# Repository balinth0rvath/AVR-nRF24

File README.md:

# RF Communication Mesh
### What is This?
A sensor network consisting a server running on a Pi and several environmental sensors based on AVR MCU's. These things are communicating each other via RF and the sensors are planned to work through a season with one charge of a 3.6V battery.  

---

### Code Structure
|Description|Module|
|------|-----------|
|Custom nRF24L01 driver in my forked Linux repo located in nRF24L01driver branch|https://github.com/balinth0rvath/linux/tree/nRF24L01driver|
|Server app and unit tests|https://github.com/balinth0rvath/AVR-nRF24/tree/master/server|
|HW related stuff (Schematics, gerber files etc...)|https://github.com/balinth0rvath/AVR-nRF24/tree/master/nRF24-design|
|Firmware of a sensor module|https://github.com/balinth0rvath/AVR-nRF24/tree/master/AVR-nRF24|

---

### Server UML

---

### Schematics

---

### Current Dev Setup (Mid of September 2021)

---

### Breadboard in Early Stage

---

### First Prototypes without Sensors

---

### Debug Screenshot, DS18B20 Sequence of Determining External Power Supply Mode

---
## Setup
### Init Yocto Build
```
$ mkdir rpi
$ cd rpi
$ git clone -b gatesgarth git://git.yoctoproject.org/poky.git
$ git clone -b gatesgarth git://git.openembedded.org/meta-openembedded
$ git clone -b gatesgarth git://git.openembedded.org/meta-raspberrypi
$ source poky/oe-init-build-env ./build
```
./build/conf/bblayers.conf
```
# POKY_BBLAYERS_CONF_VERSION is increased each time build/conf/bblayers.conf
# changes incompatibly
POKY_BBLAYERS_CONF_VERSION = "2" 

BBPATH = "${TOPDIR}"
BBFILES ?= ""

BBLAYERS ?= " \ 
  ~/yocto-builds/rpi/poky/meta \
  ~/yocto-builds/rpi/poky/meta-poky \
  ~/yocto-builds/rpi/poky/meta-yocto-bsp \
  ~/yocto-builds/rpi/meta-raspberrypi \
  ~/yocto-builds/rpi/meta-openembedded/meta-oe \
  ~/yocto-builds/rpi/meta-openembedded/meta-python \
  ~/yocto-builds/rpi/meta-openembedded/meta-networking \
  ~/yocto-builds/rpi/meta-openembedded/meta-multimedia \
  ~/yocto-builds/rpi/meta-openembedded/meta-filesystems \
  "
```

./build/conf/local.conf
```
...
MACHINE ??= "raspberrypi3"
...
DISTRO_FEATURES_append = "bluez5 bluetooth wifi systemd"
VIRTUAL-RUNTIME_init_manager = "systemd"
IMAGE_INSTALL_append = "crda iw bluez5 wpa-supplicant openssh"
```

### Create SD Card Image and SDK
```
$ cd rpi
$ . poky/oe-init-build-env
$ bitbake core-image-minimal
$ bitbake core-image-minimal -c populate_sdk
$ tmp/deploy/sdk/poky-glibc-x86_64-core-image-minimal-cortexa7t2hf-neon-vfpv4-raspberrypi3-toolchain-3.2.2.sh
```

### Install Packages
```
$ sudo apt-get install libssl-dev
```

### Build Kernel
```
$ cd <linux source root>
$ . /opt/poky/3.2.2/environment-setup-cortexa7t2hf-neon-vfpv4-poky-linux-gnueabi 
$ KERNEL=kernel7
$ make ARCH=arm CROSS_COMPILE=arm-poky-linux-gnueabi- bcm2709_defconfig
$ make ARCH=arm CROSS_COMPILE=arm-poky-linux-gnueabi- zImage modules dtbs
```

### Build Driver
```
$ cd <linux source root>
$ . /opt/poky/3.2.2/environment-setup-cortexa7t2hf-neon-vfpv4-poky-linux-gnueabi 
$ make ARCH=arm CROSS_COMPILE=arm-poky-linux-gnueabi- -C . M=drivers/char/nrf24/
$ scp nrf24.ko root@<IP of PI>:/home/root/.
```

### Server Setup
```
$ cd server
$ . /opt/poky/3.2.2/environment-setup-cortexa7t2hf-neon-vfpv4-poky-linux-gnueabi
$ make lib/libwireless.a
$ make
$ make test
$ scp server root@<IP of PI>:/home/root/.
$ scp test root@<IP of PI>:/home/root/.
```

### Server Init
```
$ insmod nrf24.ko
$ ./test
$ ./server
```

---

## Remote Debug Server
Target
```
$ gdbserver :1234 server
```
Host
```
$ arm-poky-linux-gnueabi-gdb server
(gdb) target remote <IP of PI>:1234
```
---

## Release Commits (Test Longloop)
A test named Test Longloop must pass in all release commits.
|Releas Date|Driver Branch and Commit Hash<br>Firmware and Design Branch and Commit Hash|
|----|---|
|20210517|linux@nRF24L01driver:8a4c0cdf7803df328cc4730b5077f52fee5dc932<br>AVR-nRF24@master:3eb939d17d8ff22d65403e109d810f7f85f86c85|
|20210523|linux@nRF24L01driver:8a4c0cdf7803df328cc4730b5077f52fee5dc932<br>AVR-nRF24@master:7b25dc61fc849677e8bb6358456cee5dc74c7301|
|20210531|linux@nRF24L01driver:7c86b9ca6b2d7ad1549c76c9caeeb97bab567bfb<br>AVR-nRF24@master:dd0c3b836620fbdc131a8c8d285148fa6ca5f2e6|
|20210820|inux@nRF24L01driver:7c86b9ca6b2d7ad1549c76c9caeeb97bab567bfb<br>AVR-nRF24@master:85c61a1c3e08124cf29ecca4751b73a7c155e9e8|
|20210909|linux@nRF24L01driver:f5a8eb844164f856415a3b459346a1253c0f87ff<br>AVR-nRF24@master:ca4479ed1e2c967fedf4eaf3a40d907f1cda15d0|
|20210919|linux@nRF24L01driver:f5a8eb844164f856415a3b459346a1253c0f87ff<br>AVR-nRF24@master:d2804b9a1e1fc83868c6ceb204d5eec31b9cb42f|

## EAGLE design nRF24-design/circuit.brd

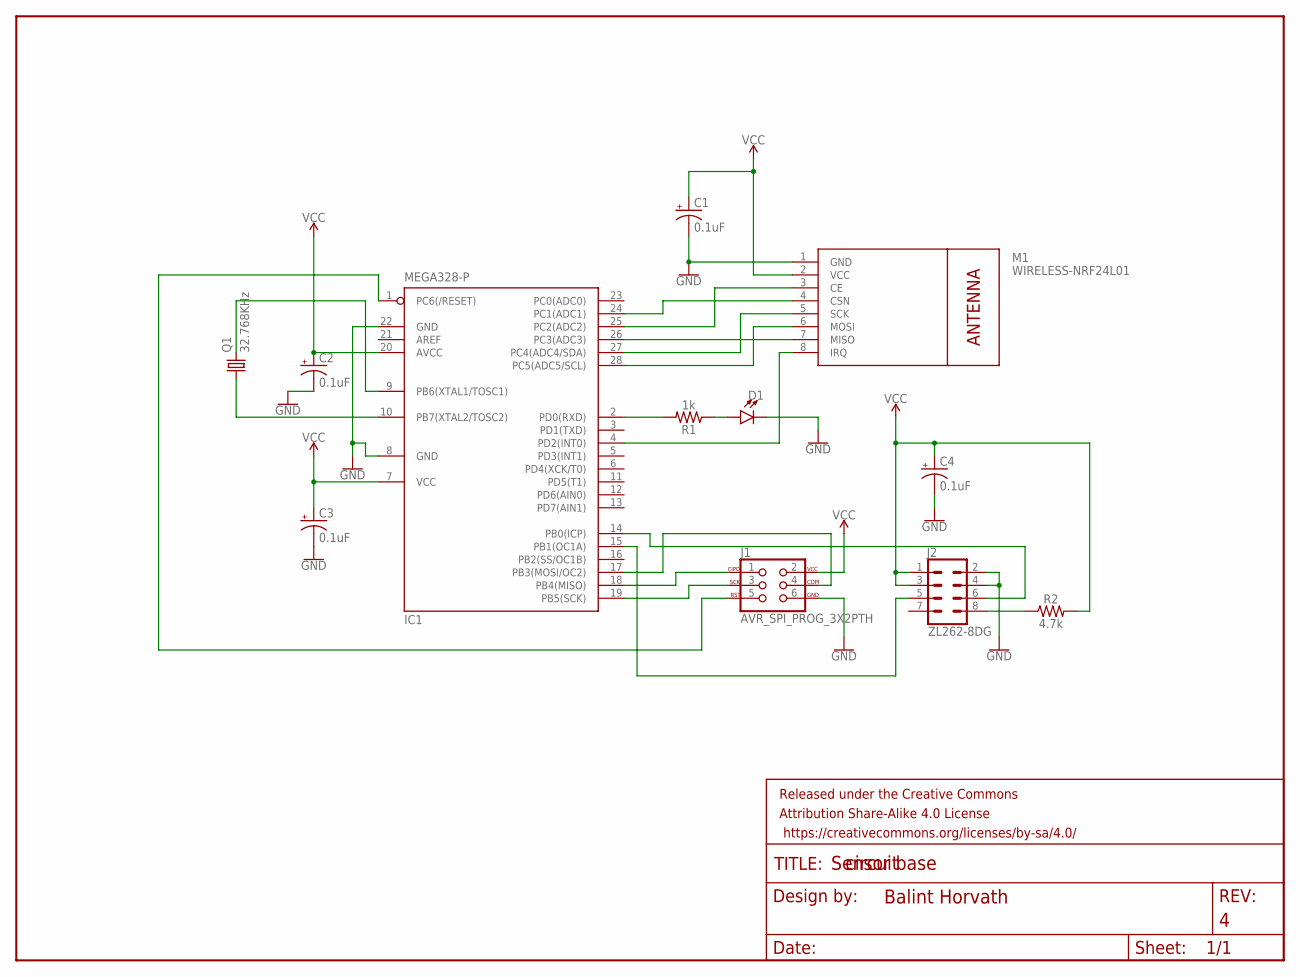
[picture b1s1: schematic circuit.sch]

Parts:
C1, C2, C3, C4: 0.1uF; CPOL-RADIAL-2.5MM-5MM
D1: LED5MM; LED_5MM
FRAME1: FRAME-LETTER; CREATIVE_COMMONS
IC1: MEGA328-P; DIL28-3
J1: AVR_SPI_PROG_3X2PTH; 2X3
J2: ZL262-8DG; 2X4
M1: WIRELESS-NRF24L01
Q1: 32.768KHz; TC26V
R1: 1k; AXIAL-0.3
R2: 4.7k; AXIAL-0.3

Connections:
GND: C1.2 (-), C2.2 (-), C3.2 (-), C4.2 (-), D1.K (C), IC1.8 (GND), IC1.22 (GND), J1.6, J2.2, J2.4, M1.1 (GND)
unnamed: IC1.9 (PB6(XTAL1/TOSC1)), Q1.2
unnamed: IC1.10 (PB7(XTAL2/TOSC2)), Q1.1
unnamed: IC1.2 (PD0(RXD)), R1.P$2 (2)
unnamed: D1.A, R1.P$1 (1)
unnamed: IC1.27 (PC4(ADC4/SDA)), M1.5 (SCK)
unnamed: IC1.4 (PD2(INT0)), M1.8 (IRQ)
unnamed: IC1.24 (PC1(ADC1)), M1.4 (CSN)
unnamed: IC1.26 (PC3(ADC3)), M1.7 (MISO)
unnamed: IC1.25 (PC2(ADC2)), M1.3 (CE)
unnamed: IC1.28 (PC5(ADC5/SCL)), M1.6 (MOSI)
unnamed: IC1.19 (PB5(SCK)), J1.3
unnamed: IC1.18 (PB4(MISO)), J1.1
unnamed: IC1.1 (PC6(/RESET)), J1.5
unnamed: IC1.17 (PB3(MOSI/OC2)), J1.4
unnamed: IC1.15 (PB1(OC1A)), J2.5
unnamed: J2.8, R2.P$1 (1)
unnamed: IC1.14 (PB0(ICP)), J2.6
VCC: C1.1 (+), C2.1 (+), C3.1 (+), C4.1 (+), IC1.7 (VCC), IC1.20 (AVCC), J1.2, J2.1, J2.3, M1.2 (VCC), R2.P$2 (2)

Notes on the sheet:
Sensor base

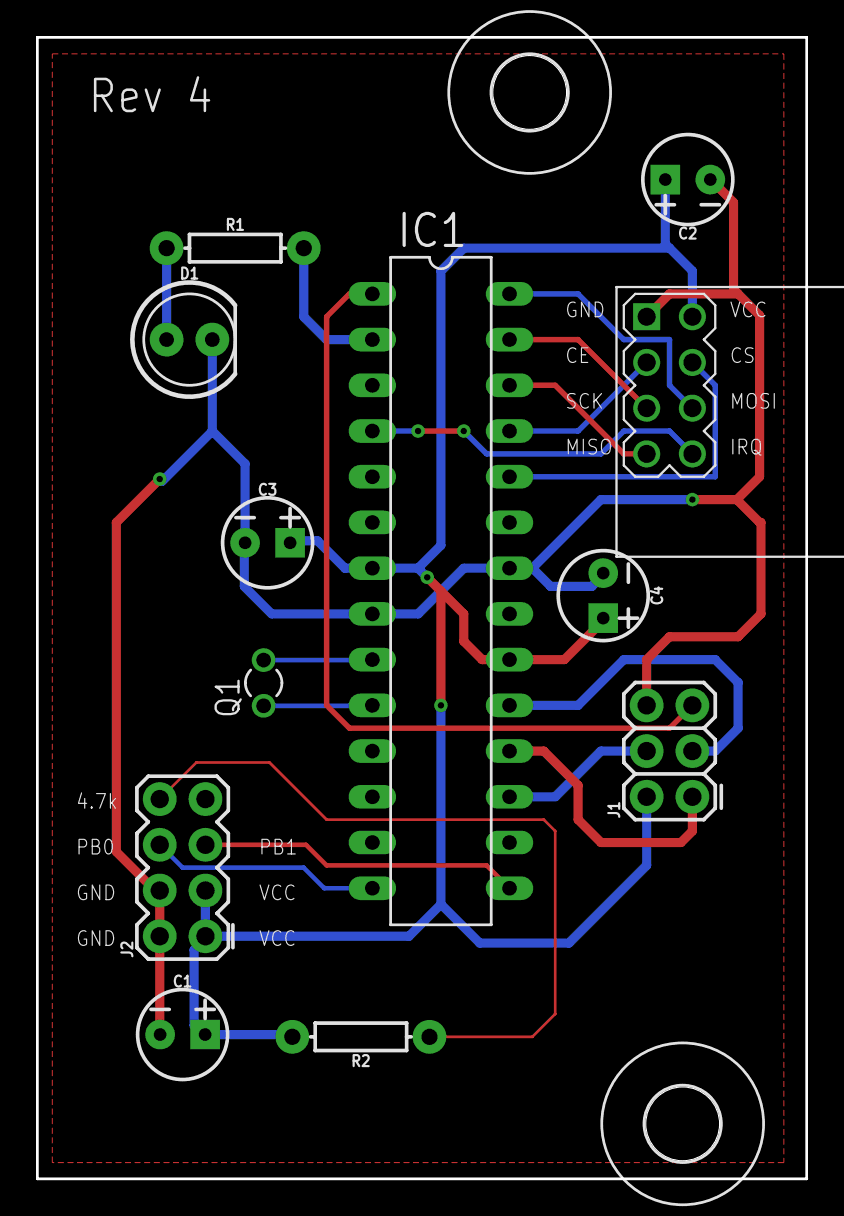
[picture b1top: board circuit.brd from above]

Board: 2 copper layers, 42.7 x 63.4 mm, 15 parts (0 on the bottom side), 19 nets.

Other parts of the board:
U$1, U$2: 4,1

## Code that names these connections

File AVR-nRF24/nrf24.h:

/*
 * nrf24.h
 *
 * Created: 4/30/2021 4:40:18 PM
 */ 


#ifndef NRF24_H_
#define NRF24_H_

#include <avr/io.h>

// Settings
#define NRF24_SET_RECEIVER                0x1
#define NRF24_PAYLOAD_LENGTH              0x4
#define NRF24_PAYLOAD_BUFFER_SIZE         0x50  

// SPI Port
#define NRF24_DDR                         DDRC
#define NRF24_PORT                        PORTC
#define NRF24_PIN                         PINC

// IRQ Port
#define NRF24_DDR_IRQ                     DDRD
#define NRF24_PORT_IRQ                    PORTD

// SPI&CE pin settings
#define NRF24_GPIO_CE                     PC2							
#define NRF24_GPIO_SCLK                   PC4								
#define NRF24_GPIO_MOSI                   PC5								
#define NRF24_GPIO_CSN                    PC1								
#define NRF24_GPIO_MISO                   PC3							
#define NRF24_SPI_HALF_CLK                1							

// IRQ pin settings
#define NRF24_GPIO_IRQ                    PD2								

// nRF24 commands
#define NRF24_CMD_R_REGISTER              0x00
#define NRF24_CMD_W_REGISTER              0x20
#define NRF24_CMD_R_RX_PAYLOAD            0x61
#define NRF24_CMD_W_TX_PAYLOAD            0xa0
#define NRF24_CMD_FLUSH_TX                0xe1
#define NRF24_CMD_FLUSH_RX                0xe2
#define NRF24_CMD_REUSE_TX_PL             0xe3
#define NRF24_CMD_ACTIVATE                0x50
#define NRF24_CMD_R_RX_PL_WID             0x60
#define NRF24_CMD_W_ACK_PAYLOAD           0xa8
#define NRF24_CMD_W_TX_PAYLOAD_NO_ACK			0xb0
#define NRF24_CMD_NOP                     0xff

// nRF24 registers
#define NRF24_REG_CONFIG                  0x00
#define NRF24_REG_EN_AA                   0x01
#define NRF24_REG_EN_RXADDR               0x02
#define NRF24_REG_SETUP_AW                0x03
#define NRF24_REG_SETUP_RETR              0x04
#define NRF24_REG_RF_CH                   0x05
#define NRF24_REG_RF_SETUP                0x06
#define NRF24_REG_STATUS                  0x07
#define NRF24_REG_OBSERVE_TX              0x08
#define NRF24_REG_CD                      0x09
#define NRF24_REG_RX_ADDR_P0              0x0a
#define NRF24_REG_RX_ADDR_P1              0x0b
#define NRF24_REG_RX_ADDR_P2              0x0c
#define NRF24_REG_RX_ADDR_P3              0x0d
#define NRF24_REG_RX_ADDR_P4              0x0e
#define NRF24_REG_RX_ADDR_P5              0x0f
#define NRF24_REG_TX_ADDR                 0x10
#define NRF24_REG_RX_PW_P0                0x11
#define NRF24_REG_RX_PW_P1                0x12
#define NRF24_REG_RX_PW_P2                0x13
#define NRF24_REG_RX_PW_P3                0x14
#define NRF24_REG_RX_PW_P4                0x15
#define NRF24_REG_RX_PW_P5                0x16
#define NRF24_REG_FIFO_STATUS             0x17
#define NRF24_REG_DYNPD                   0x1c
#define NRF24_REG_FEATURE                 0x1d

#define NRF24_REG_STATUS_DEFAULT          0x0e

typedef struct  {
	uint8_t id;
	uint8_t source_address;
	uint8_t value;
	uint8_t aux;
} nrf24_payload_buffer_item_t;

void nrf24_init(uint8_t use_spi);
int nrf24_check_device();
void nrf24_set_receiver();
void nrf24_set_transmitter();
void nrf24_set_rx_address_p0(uint8_t* address);
void nrf24_set_tx_address(uint8_t* address);
void nrf24_get_rx_address_p0(uint8_t* address);
void nrf24_get_tx_address(uint8_t* address);
void nrf24_receive_irq(void);
void nrf24_transmit_irq(void);
void nrf24_receive_poll(void);
void nrf24_transmit_packet(char* payload, uint8_t* status);
void nrf24_flush_tx(void);
void nrf24_flush_rx(void);
void nrf24_get_buffer_head(nrf24_payload_buffer_item_t* item);
uint8_t nrf24_get_status(void);
uint8_t nrf4_message_received(void);

#endif /* NRF24_H_ */

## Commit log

2021-04-30 Setup Atmel Studio
2021-04-30 nrf24: Implement basic bitbang driver functions
2021-04-30 Create LICENSE
2021-05-01 Fix bugs in nrf24 init
2021-05-01 Fix bug with MISO pin
2021-05-02 Create basic receiver. Refactor code
2021-05-03 Refactor code. Replace 16bit variables with 8bit, if possibble
2021-05-03 Implement transmitter
2021-05-04 Transmitter MVP
2021-05-05 Implement indicators
2021-05-07 Implement interrupt handling
2021-05-07 Implement interrupt handling in tx mode too
2021-05-07 Prepare switching between built in SPI and bitbang SPI
2021-05-08 Use HW SPI
2021-05-08 Check HW SPI receiver. Put half cycle wait into bb
2021-05-10 Implement ring buffer
2021-05-14 Separate receiver and transmitter
2021-05-16 Implement handshaking
2021-05-17 Prepare test
2021-05-17 Add unit test
2021-05-19 Prepare test framework
2021-05-22 Implement structure of test cases. Implement open driver test case
2021-05-23 Implement test cases
2021-05-23 Upload schematics
2021-05-23 Setup indicator led. Set, get RXP0, TX addresses
2021-05-23 Fix test lib link
2021-05-23 Add binaries to gitignore
2021-05-30 Add setup hint for MCU
2021-05-30 Use LED blinking for feedback
2021-05-30 New tests with different addresses
2021-05-30 Match address with tests
2021-05-30 Investigate address problem
2021-05-30 Investigate address problem - tests
2021-05-30 Create repeated test
2021-05-30 Tune timing
2021-05-30 Tune test parameters
2021-05-31 Refactor code
2021-05-31 Setup test cases with new address
2021-05-31 Setup MCU with matching address
2021-05-31 Update release list
2021-08-15 Add eagle files
2021-08-17 Finish schematics. Create board files. Create Gerber files
2021-08-17 Fix design. Add image of schematics
2021-08-17 Create Gerber files
2021-08-17 Create Gerber files for jlcpcb
2021-08-19 Create server project skeleton
2021-08-19 Create base structure of server
2021-08-19 Add server to README
2021-08-19 server: Create device interface
2021-08-20 server: nrf24 device impl skeleton
2021-08-20 Update gitignore
2021-08-20 server: create device builder
2021-08-23 design: Fix errors (missing power and cipo connections)
2021-08-24 design: add power connectors. Add sensor connectors
2021-08-24 server: Implement controller
2021-08-25 server: Implement send, set address and close
2021-08-25 server: add uml
2021-08-25 mcu: Implement one time dummy sender. Separate it from test longloop
2021-08-25 server: Implement receiver
2021-08-30 design: Upload photo of PCB
2021-08-30 Update readme regarding the pictures of PCB
2021-08-31 mcu: Switch to ATMEGA 48PU
2021-08-31 mcu: Refactor tabs
2021-08-31 mcu: Refactor folder structure
2021-08-31 mcu: Create header of DS18B20 temperature sensor driver
2021-08-31 mcu: Eliminate warnings. Refactor tabs
2021-09-01 mcu: Implement initialization procedure
2021-09-01 mcu: Implement commands and full read temperature
2021-09-01 mcu: add author
2021-09-01 mcu: Add author to all sources
2021-09-07 mcu: Set debug mode in project
2021-09-07 mcu: Fix ds18b20 driver timings and sequences
2021-09-07 mcu: Create blink test and ds18b20 test
2021-09-07 mcu: Put an oscilloscope view of full read sequence of DS18B20 into readme
2021-09-08 mcu: Implement DS18B20 read power supply
2021-09-09 mcu: RELEASE (48PA 10Mhz debugwire)
2021-09-09 test: temperature sensor test
2021-09-09 mcu: Setup temperature sensor test
2021-09-16 mcu: Implement nRF24 power down
2021-09-16 server: Create skeleton of common server/unit test structure
2021-09-16 server: Implement long loop test
2021-09-16 server: Refactor wireless interface
2021-09-18 server: Update UML
2021-09-18 server: Fix interfaces in UML
2021-09-18 server: Implement test long loop tc
2021-09-19 mcu: Release modification, sync with test
2021-09-19 server: Move tests under server directory. Delete old tests
2021-09-19 mcu: Add photo of current setup
2021-09-19 common: Sync readme with current status
2021-09-19 common: Fix doc issues in readme
2021-09-20 server: Small fixes: add constness, remove unnecessary creation of rvalue etc...
2021-10-21 mcu: Setup sleep block. Use internal oscillator from now
2021-10-21 mcu: Create basic timer function
2021-10-22 mcu: Implement periodic POWER_SAVE using external 32.768KHz crystal. Switch back to 328
2021-10-23 mcu: Create new project for c++ solution
2021-10-25 mcu: Rewrite nrf24 driver and longloop test in c++
2021-10-26 mcu: Rewrite ds18b20 driver in c++
2021-11-01 design: Align dimensions to box. Add more decoupling capacitors and labels

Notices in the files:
parts and their libraries:
SparkFun-Capacitors: Licensing: Creative Commons ShareAlike 4.0 International - https://creativecommons.org/licenses/by-sa/4.0
diy-modules: Released under the Creative Commons Attribution 4.0 International License: http://creativecommons.org/licenses/by/4.0
